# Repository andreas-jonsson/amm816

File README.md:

# AMM816

A homebrew CPU built from discrete logic.

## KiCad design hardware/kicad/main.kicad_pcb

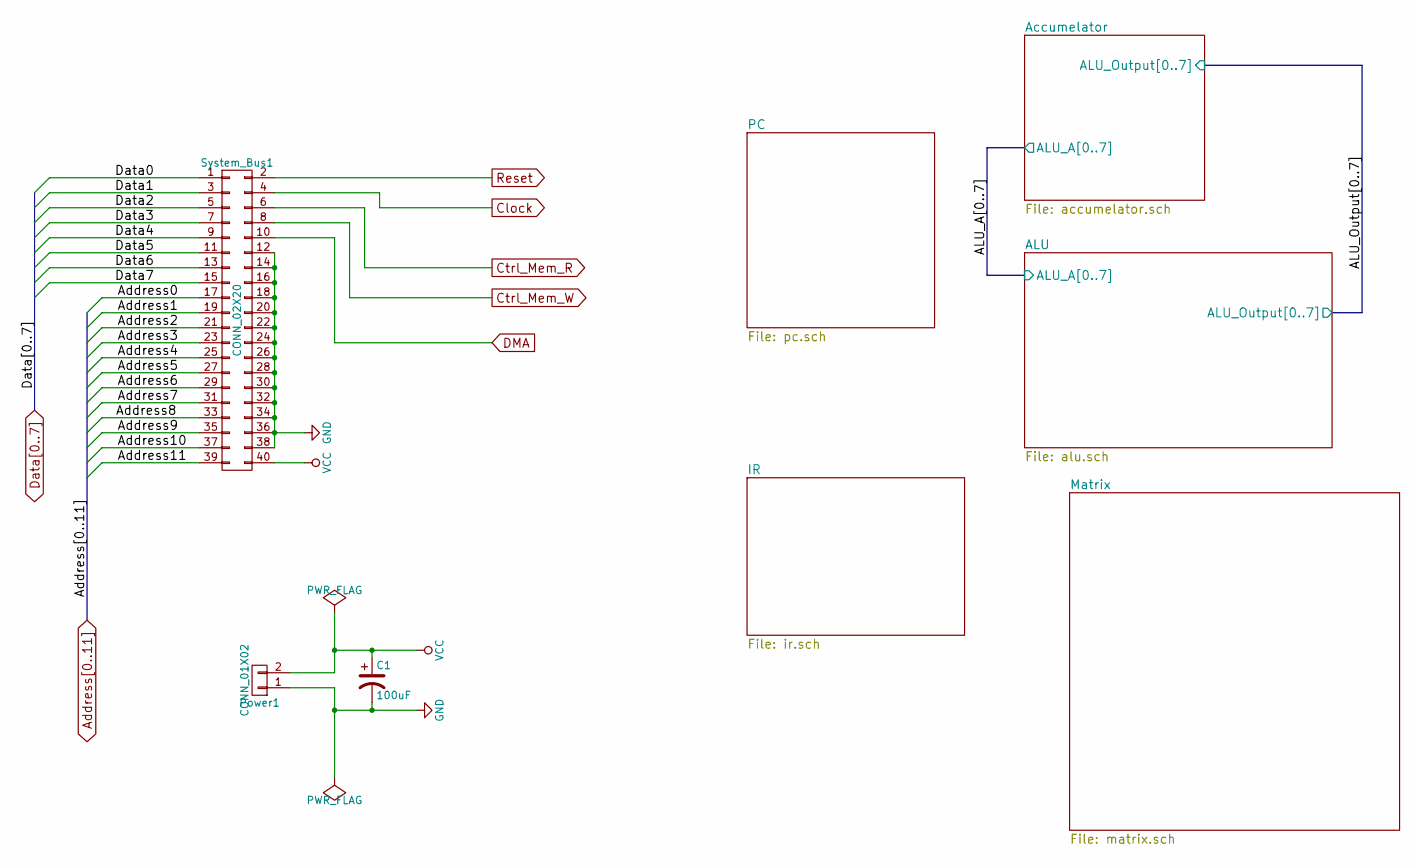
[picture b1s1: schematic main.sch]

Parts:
C1: 100uF; C_Radial_D5_L11_P2.5
Power1: CONN_01X02; Molex_KK-6410-02_02x2.54mm_Straight
System_Bus1: CONN_02X20; Pin_Header_Straight_2x20_Pitch2.00mm

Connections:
Address0: System_Bus1.17; also elsewhere on the board
Address1: System_Bus1.19; also elsewhere on the board
Address2: System_Bus1.21; also elsewhere on the board
Address3: System_Bus1.23; also elsewhere on the board
Address4: System_Bus1.25; also elsewhere on the board
Address5: System_Bus1.27; also elsewhere on the board
Address6: System_Bus1.29; also elsewhere on the board
Address7: System_Bus1.31; also elsewhere on the board
Address8: System_Bus1.33; also elsewhere on the board
Address9: System_Bus1.35; also elsewhere on the board
Address10: System_Bus1.37; also elsewhere on the board
Address11: System_Bus1.39; also elsewhere on the board
Clock: System_Bus1.4; also elsewhere on the board
Ctrl_Mem_R: System_Bus1.6; also elsewhere on the board
Ctrl_Mem_W: System_Bus1.8; also elsewhere on the board
DMA: System_Bus1.10; also elsewhere on the board
Data0: System_Bus1.1; also elsewhere on the board
Data1: System_Bus1.3; also elsewhere on the board
Data2: System_Bus1.5; also elsewhere on the board
Data3: System_Bus1.7; also elsewhere on the board
Data4: System_Bus1.9; also elsewhere on the board
Data5: System_Bus1.11; also elsewhere on the board
Data6: System_Bus1.13; also elsewhere on the board
Data7: System_Bus1.15; also elsewhere on the board
GND: C1.2, Power1.1, System_Bus1.12, System_Bus1.14, System_Bus1.16, System_Bus1.18, System_Bus1.20, System_Bus1.22, System_Bus1.24, System_Bus1.26, System_Bus1.28, System_Bus1.30, System_Bus1.32, System_Bus1.34, System_Bus1.36, System_Bus1.38; also elsewhere on the board
Reset: System_Bus1.2; also elsewhere on the board
VCC: C1.1, Power1.2, System_Bus1.40; also elsewhere on the board

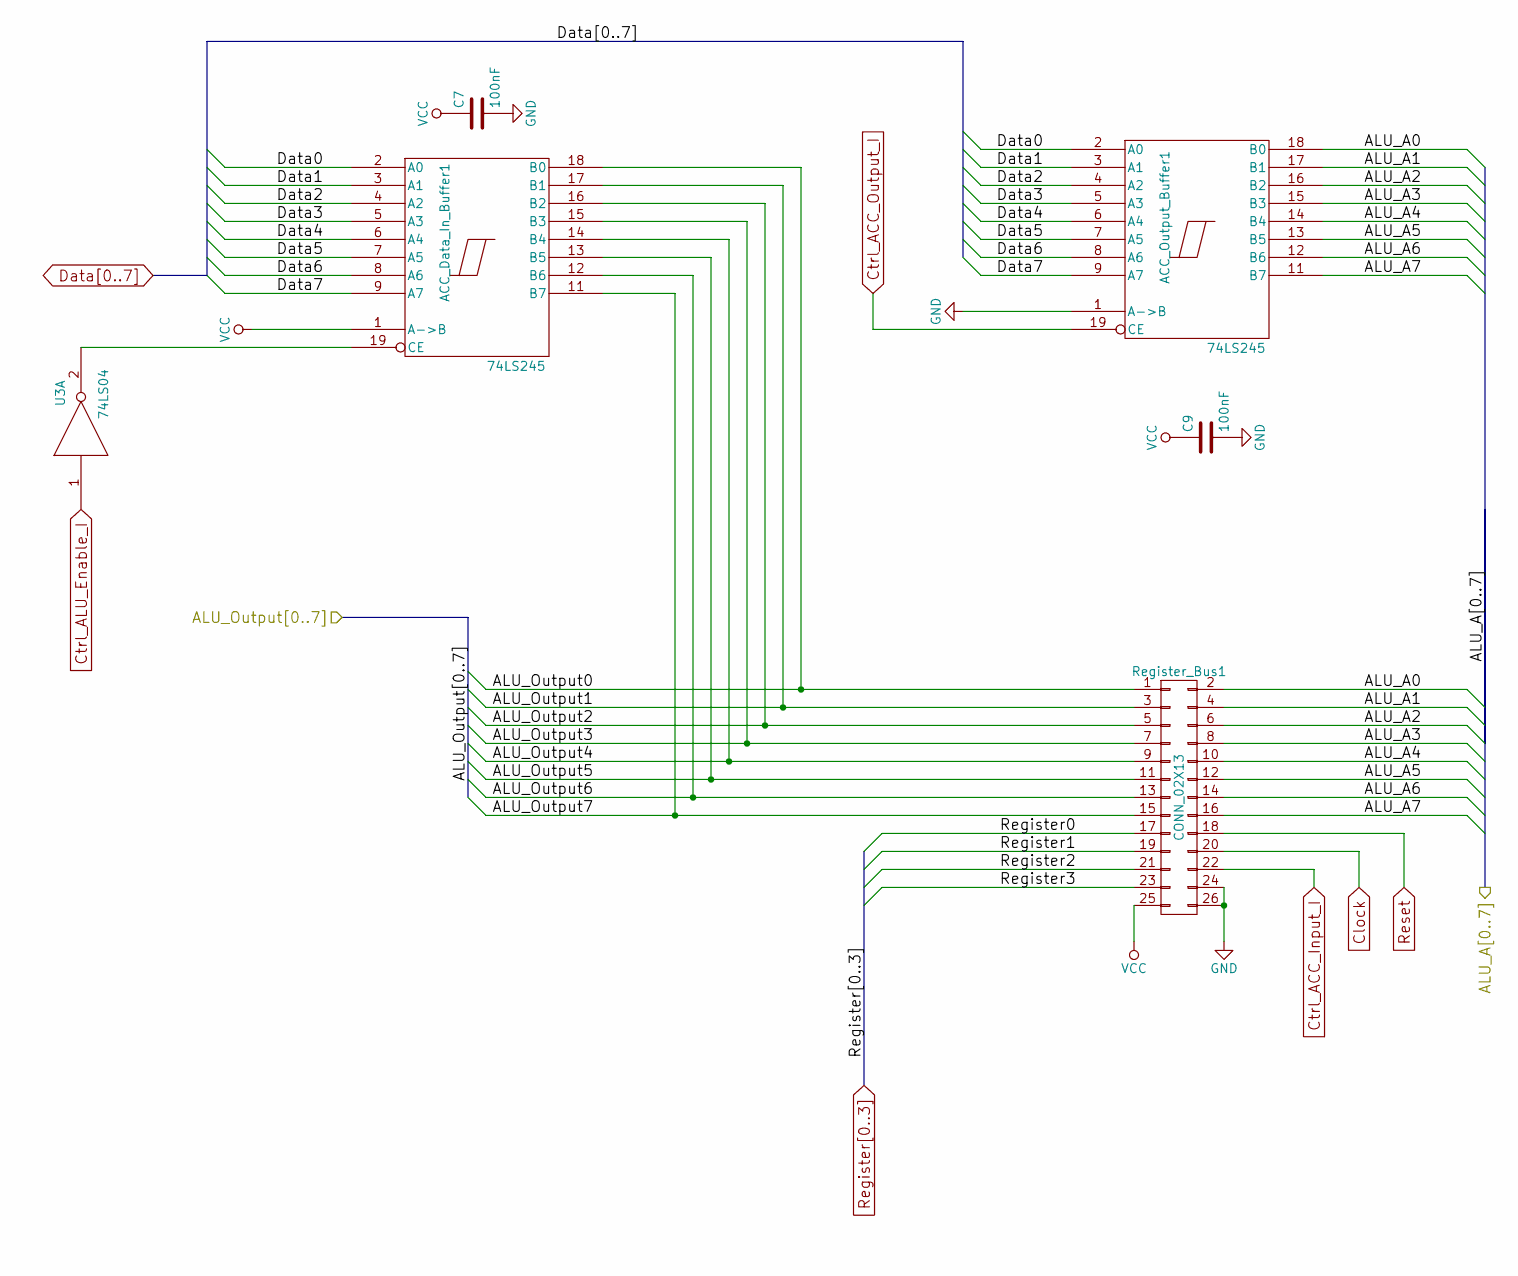
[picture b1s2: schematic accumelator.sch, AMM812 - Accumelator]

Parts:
ACC_Data_In_Buffer1: 74LS245; DIP-20_W7.62mm
ACC_Output_Buffer1: 74LS245; DIP-20_W7.62mm
C7, C9: 100nF; C_Disc_D3_P2.5
Register_Bus1: CONN_02X13; Pin_Header_Straight_2x13_Pitch2.00mm
U3: 74LS04; DIP-14_W7.62mm

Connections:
/ALU/ALU_A0: ACC_Output_Buffer1.18 (B0), Register_Bus1.2; also elsewhere on the board
/ALU/ALU_A1: ACC_Output_Buffer1.17 (B1), Register_Bus1.4; also elsewhere on the board
/ALU/ALU_A2: ACC_Output_Buffer1.16 (B2), Register_Bus1.6; also elsewhere on the board
/ALU/ALU_A3: ACC_Output_Buffer1.15 (B3), Register_Bus1.8; also elsewhere on the board
/ALU/ALU_A4: ACC_Output_Buffer1.14 (B4), Register_Bus1.10; also elsewhere on the board
/ALU/ALU_A5: ACC_Output_Buffer1.13 (B5), Register_Bus1.12; also elsewhere on the board
/ALU/ALU_A6: ACC_Output_Buffer1.12 (B6), Register_Bus1.14; also elsewhere on the board
/ALU/ALU_A7: ACC_Output_Buffer1.11 (B7), Register_Bus1.16; also elsewhere on the board
/ALU/ALU_Output0: ACC_Data_In_Buffer1.18 (B0), Register_Bus1.1; also elsewhere on the board
/ALU/ALU_Output1: ACC_Data_In_Buffer1.17 (B1), Register_Bus1.3; also elsewhere on the board
/ALU/ALU_Output2: ACC_Data_In_Buffer1.16 (B2), Register_Bus1.5; also elsewhere on the board
/ALU/ALU_Output3: ACC_Data_In_Buffer1.15 (B3), Register_Bus1.7; also elsewhere on the board
/ALU/ALU_Output4: ACC_Data_In_Buffer1.14 (B4), Register_Bus1.9; also elsewhere on the board
/ALU/ALU_Output5: ACC_Data_In_Buffer1.13 (B5), Register_Bus1.11; also elsewhere on the board
/ALU/ALU_Output6: ACC_Data_In_Buffer1.12 (B6), Register_Bus1.13; also elsewhere on the board
/ALU/ALU_Output7: ACC_Data_In_Buffer1.11 (B7), Register_Bus1.15; also elsewhere on the board
Clock: Register_Bus1.20; also elsewhere on the board
Ctrl_ACC_Input_I: Register_Bus1.22; also elsewhere on the board
Ctrl_ACC_Output_I: ACC_Output_Buffer1.19 (CE); also elsewhere on the board
Ctrl_ALU_Enable_I: U3.1; also elsewhere on the board
Data0: ACC_Data_In_Buffer1.2 (A0), ACC_Output_Buffer1.2 (A0); also elsewhere on the board
Data1: ACC_Data_In_Buffer1.3 (A1), ACC_Output_Buffer1.3 (A1); also elsewhere on the board
Data2: ACC_Data_In_Buffer1.4 (A2), ACC_Output_Buffer1.4 (A2); also elsewhere on the board
Data3: ACC_Data_In_Buffer1.5 (A3), ACC_Output_Buffer1.5 (A3); also elsewhere on the board
Data4: ACC_Data_In_Buffer1.6 (A4), ACC_Output_Buffer1.6 (A4); also elsewhere on the board
Data5: ACC_Data_In_Buffer1.7 (A5), ACC_Output_Buffer1.7 (A5); also elsewhere on the board
Data6: ACC_Data_In_Buffer1.8 (A6), ACC_Output_Buffer1.8 (A6); also elsewhere on the board
Data7: ACC_Data_In_Buffer1.9 (A7), ACC_Output_Buffer1.9 (A7); also elsewhere on the board
GND: ACC_Data_In_Buffer1.10 (GND), ACC_Output_Buffer1.1 (A->B), ACC_Output_Buffer1.10 (GND), C7.2, C9.2, Register_Bus1.24, Register_Bus1.26, U3.7 (GND); also elsewhere on the board
unnamed: ACC_Data_In_Buffer1.19 (CE), U3.2
Register0: Register_Bus1.17; also elsewhere on the board
Register1: Register_Bus1.19; also elsewhere on the board
Register2: Register_Bus1.21; also elsewhere on the board
Register3: Register_Bus1.23; also elsewhere on the board
Reset: Register_Bus1.18; also elsewhere on the board
VCC: ACC_Data_In_Buffer1.1 (A->B), ACC_Data_In_Buffer1.20 (VCC), ACC_Output_Buffer1.20 (VCC), C7.1, C9.1, Register_Bus1.25, U3.14 (VCC); also elsewhere on the board

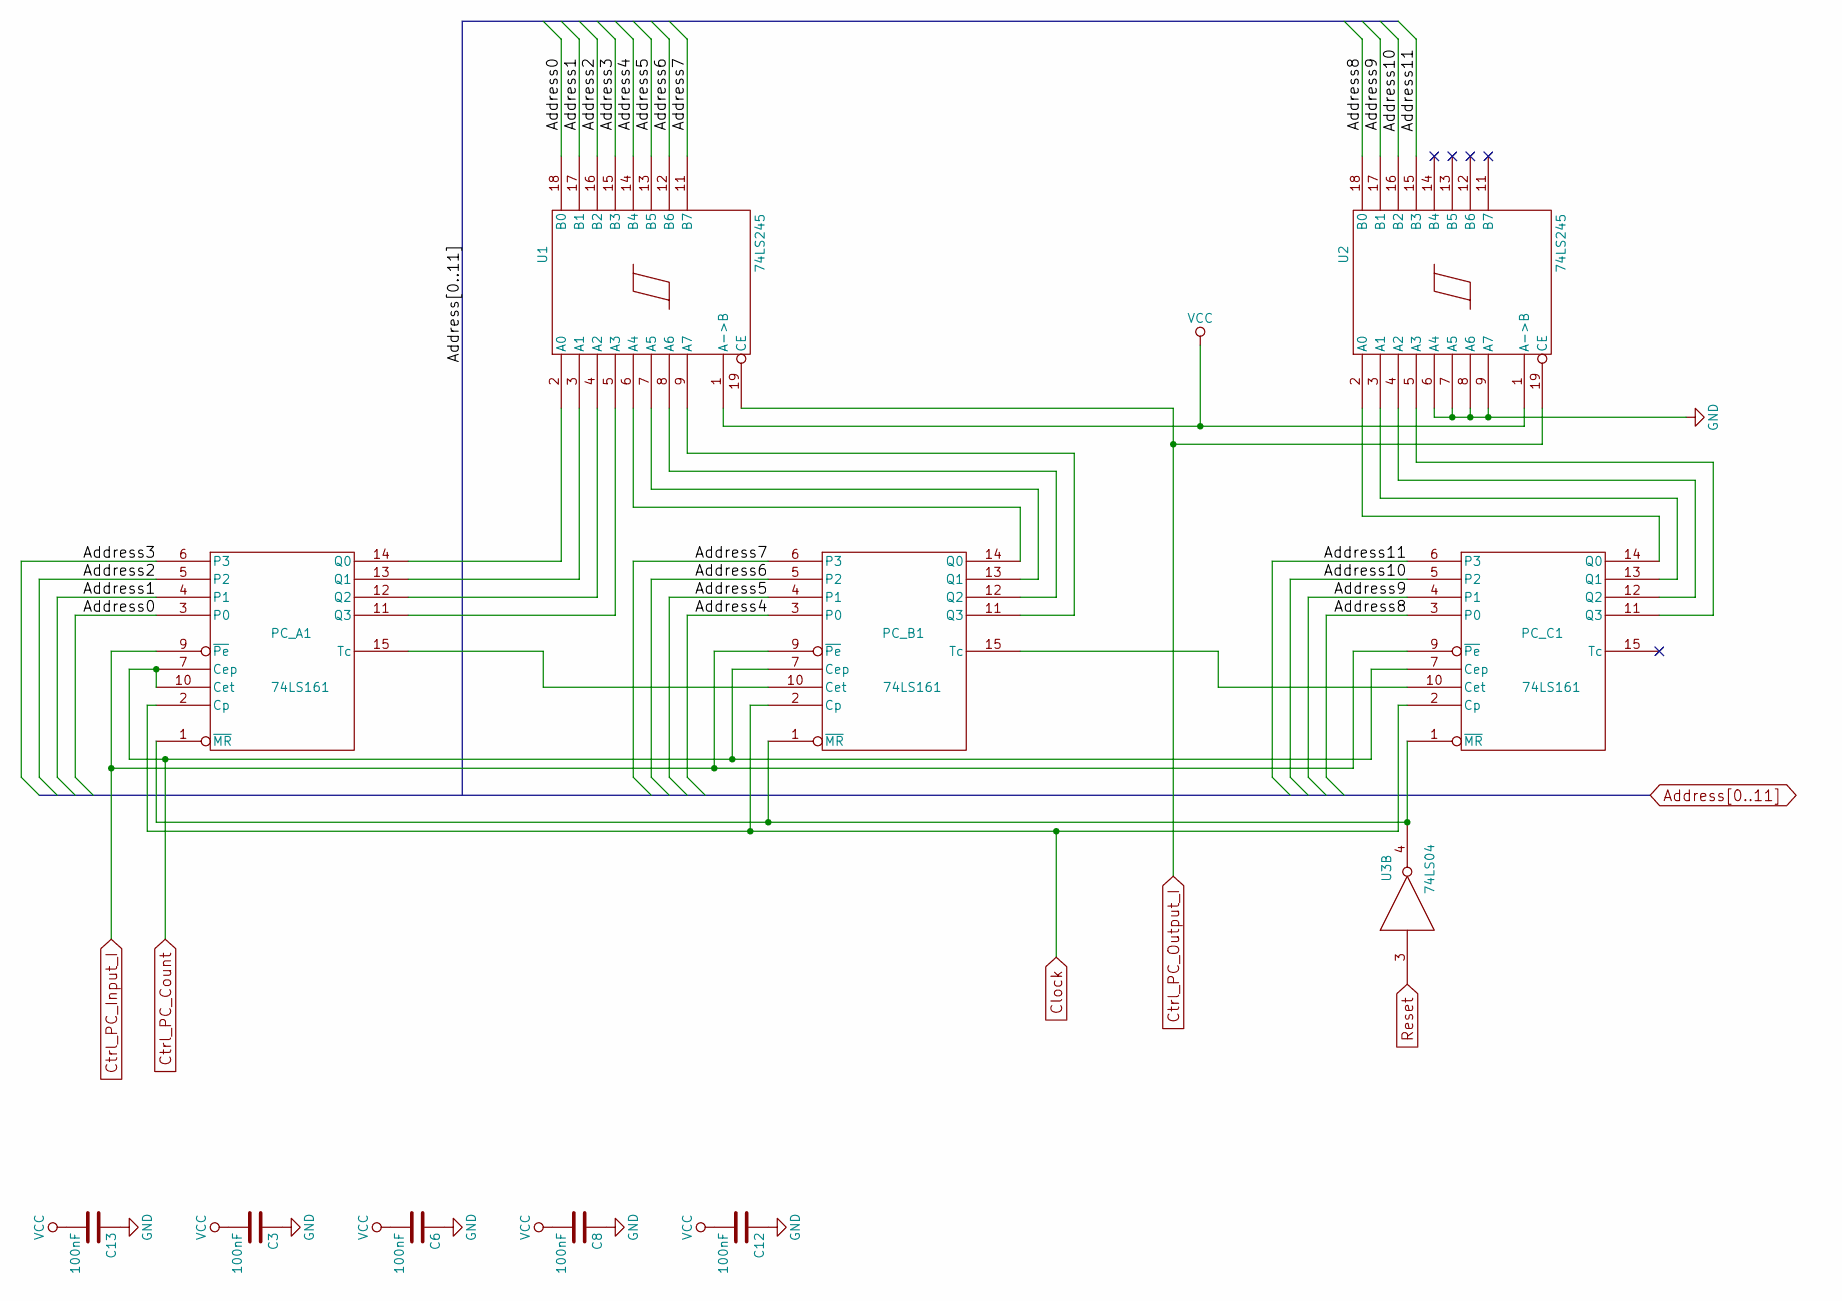
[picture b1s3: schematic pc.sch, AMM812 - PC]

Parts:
C3, C6, C8, C12, C13: 100nF; C_Disc_D3_P2.5
PC_A1: 74LS161; DIP-16_W7.62mm
PC_B1: 74LS161; DIP-16_W7.62mm
PC_C1: 74LS161; DIP-16_W7.62mm
U1, U2: 74LS245; DIP-20_W7.62mm
U3: 74LS04; DIP-14_W7.62mm

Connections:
Address0: PC_A1.3 (P0), U1.18 (B0); also elsewhere on the board
Address1: PC_A1.4 (P1), U1.17 (B1); also elsewhere on the board
Address2: PC_A1.5 (P2), U1.16 (B2); also elsewhere on the board
Address3: PC_A1.6 (P3), U1.15 (B3); also elsewhere on the board
Address4: PC_B1.3 (P0), U1.14 (B4); also elsewhere on the board
Address5: PC_B1.4 (P1), U1.13 (B5); also elsewhere on the board
Address6: PC_B1.5 (P2), U1.12 (B6); also elsewhere on the board
Address7: PC_B1.6 (P3), U1.11 (B7); also elsewhere on the board
Address8: PC_C1.3 (P0), U2.18 (B0); also elsewhere on the board
Address9: PC_C1.4 (P1), U2.17 (B1); also elsewhere on the board
Address10: PC_C1.5 (P2), U2.16 (B2); also elsewhere on the board
Address11: PC_C1.6 (P3), U2.15 (B3); also elsewhere on the board
Clock: PC_A1.2 (Cp), PC_B1.2 (Cp), PC_C1.2 (Cp); also elsewhere on the board
Ctrl_PC_Count: PC_A1.7 (Cep), PC_A1.10 (Cet), PC_B1.7 (Cep), PC_C1.7 (Cep); also elsewhere on the board
Ctrl_PC_Input_I: PC_A1.9 (~Pe), PC_B1.9 (~Pe), PC_C1.9 (~Pe); also elsewhere on the board
Ctrl_PC_Output_I: U1.19 (CE), U2.19 (CE); also elsewhere on the board
GND: C3.1, C6.1, C8.1, C12.1, C13.1, PC_A1.8 (GND), PC_B1.8 (GND), PC_C1.8 (GND), U1.10 (GND), U2.6 (A4), U2.7 (A5), U2.8 (A6), U2.9 (A7), U2.10 (GND), U3.7 (GND); also elsewhere on the board
unnamed: PC_A1.1 (~MR), PC_B1.1 (~MR), PC_C1.1 (~MR), U3.4
unnamed: PC_A1.11 (Q3), U1.5 (A3)
unnamed: PC_A1.12 (Q2), U1.4 (A2)
unnamed: PC_A1.13 (Q1), U1.3 (A1)
unnamed: PC_A1.14 (Q0), U1.2 (A0)
unnamed: PC_A1.15 (Tc), PC_B1.10 (Cet)
unnamed: PC_B1.11 (Q3), U1.9 (A7)
unnamed: PC_B1.12 (Q2), U1.8 (A6)
unnamed: PC_B1.13 (Q1), U1.7 (A5)
unnamed: PC_B1.14 (Q0), U1.6 (A4)
unnamed: PC_B1.15 (Tc), PC_C1.10 (Cet)
unnamed: PC_C1.11 (Q3), U2.5 (A3)
unnamed: PC_C1.12 (Q2), U2.4 (A2)
unnamed: PC_C1.13 (Q1), U2.3 (A1)
unnamed: PC_C1.14 (Q0), U2.2 (A0)
Reset: U3.3; also elsewhere on the board
VCC: C3.2, C6.2, C8.2, C12.2, C13.2, PC_A1.16 (VCC), PC_B1.16 (VCC), PC_C1.16 (VCC), U1.1 (A->B), U1.20 (VCC), U2.1 (A->B), U2.20 (VCC), U3.14 (VCC); also elsewhere on the board

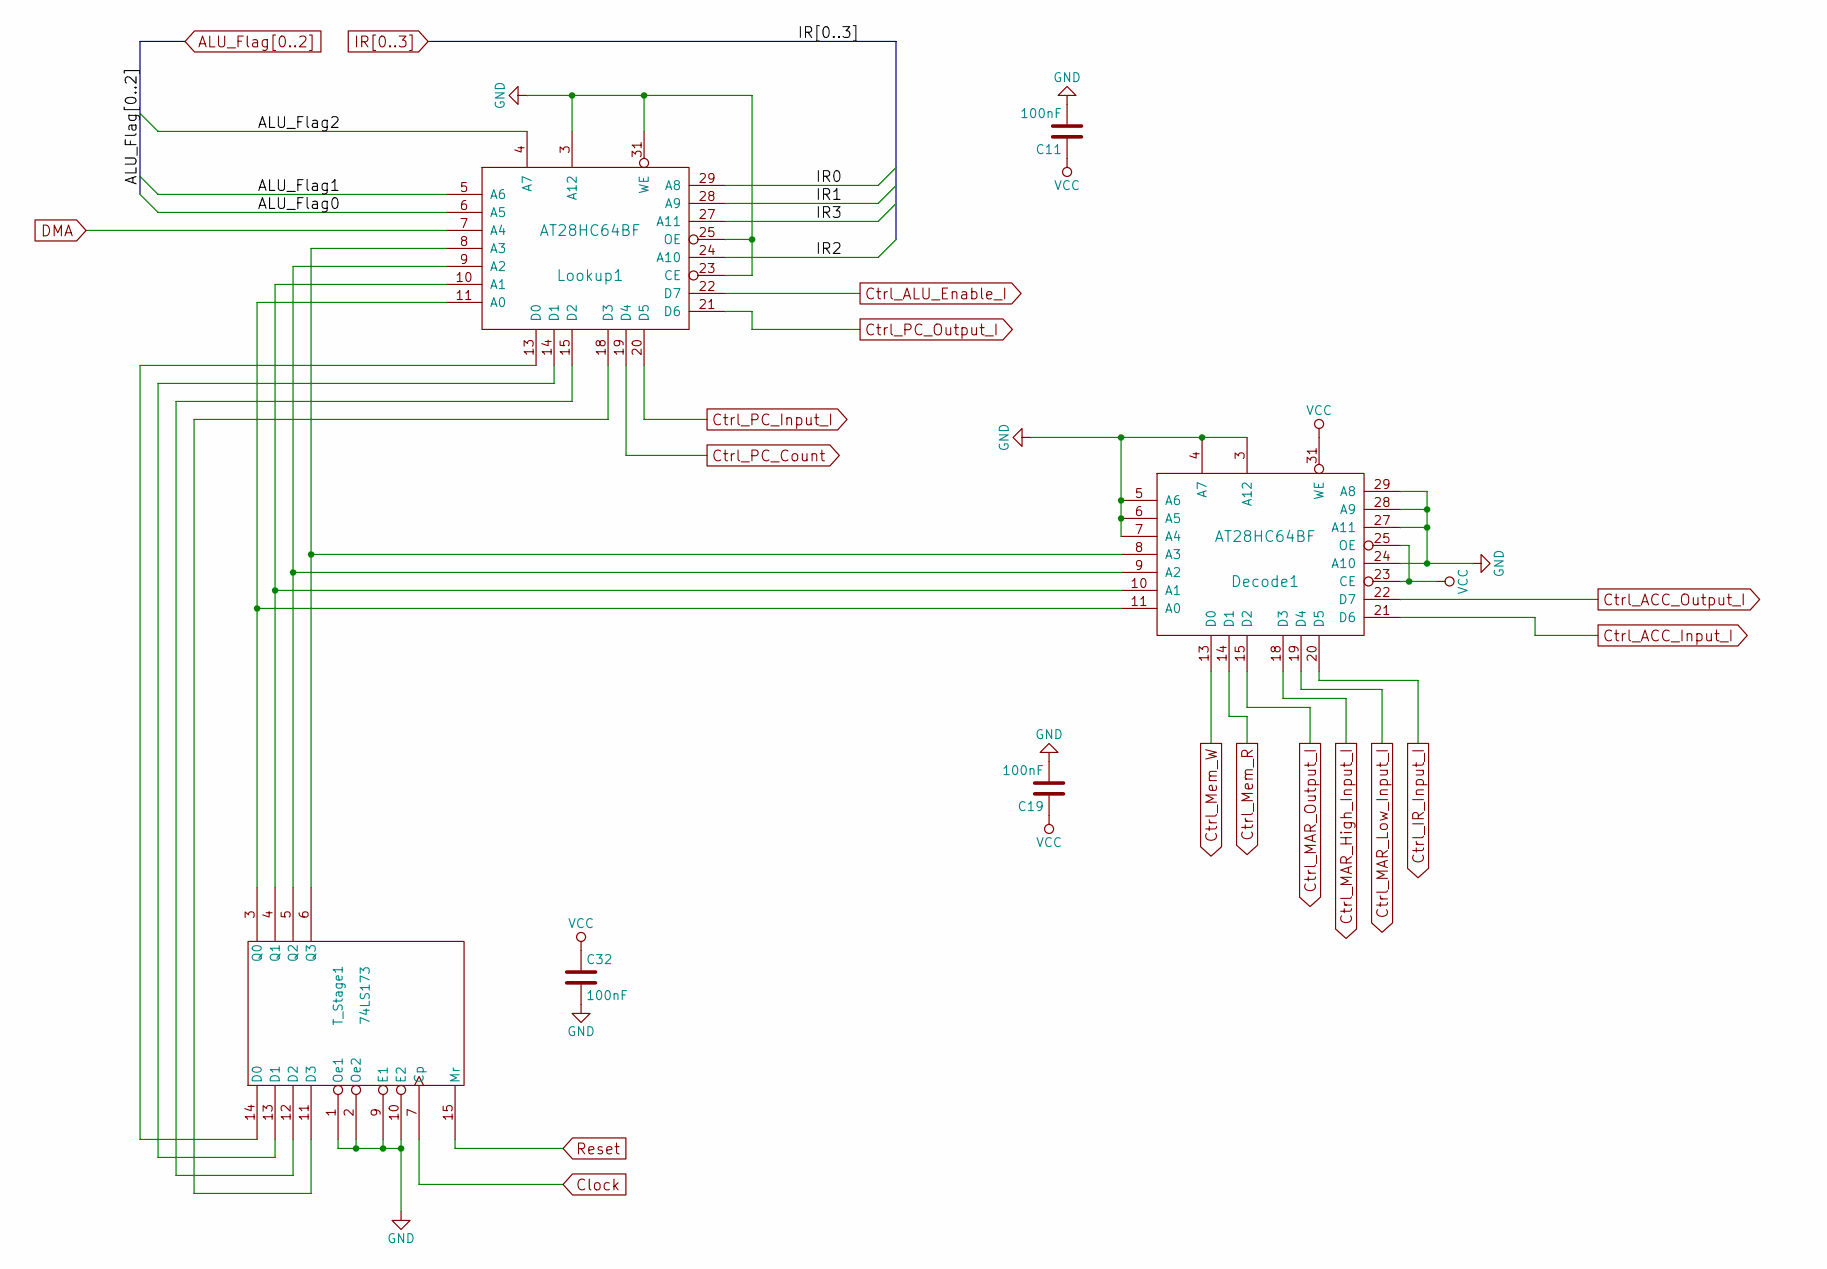
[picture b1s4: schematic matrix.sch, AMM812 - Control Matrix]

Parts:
C11, C19, C32: 100nF; C_Disc_D3_P2.5
Decode1: AT28HC64BF; PLCC-32_THT-Socket_bugfix
Lookup1: AT28HC64BF; PLCC-32_THT-Socket_bugfix
T_Stage1: 74LS173; DIP-16_W7.62mm

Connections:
ALU_Flag0: Lookup1.6 (A5); also elsewhere on the board
ALU_Flag1: Lookup1.5 (A6); also elsewhere on the board
ALU_Flag2: Lookup1.4 (A7); also elsewhere on the board
Clock: T_Stage1.7 (Cp); also elsewhere on the board
Ctrl_ACC_Input_I: Decode1.21 (D6); also elsewhere on the board
Ctrl_ACC_Output_I: Decode1.22 (D7); also elsewhere on the board
Ctrl_ALU_Enable_I: Lookup1.22 (D7); also elsewhere on the board
Ctrl_IR_Input_I: Decode1.20 (D5); also elsewhere on the board
Ctrl_MAR_High_Input_I: Decode1.18 (D3); also elsewhere on the board
Ctrl_MAR_Low_Input_I: Decode1.19 (D4); also elsewhere on the board
Ctrl_MAR_Output_I: Decode1.15 (D2); also elsewhere on the board
Ctrl_Mem_R: Decode1.14 (D1); also elsewhere on the board
Ctrl_Mem_W: Decode1.13 (D0); also elsewhere on the board
Ctrl_PC_Count: Lookup1.19 (D4); also elsewhere on the board
Ctrl_PC_Input_I: Lookup1.20 (D5); also elsewhere on the board
Ctrl_PC_Output_I: Lookup1.21 (D6); also elsewhere on the board
DMA: Lookup1.7 (A4); also elsewhere on the board
GND: C11.2, C19.2, C32.2, Decode1.3 (A12), Decode1.4 (A7), Decode1.5 (A6), Decode1.6 (A5), Decode1.7 (A4), Decode1.16 (GND), Decode1.24 (A10), Decode1.27 (A11), Decode1.28 (A9), Decode1.29 (A8), Lookup1.3 (A12), Lookup1.16 (GND), Lookup1.23 (CE), Lookup1.25 (OE), Lookup1.31 (WE), T_Stage1.1 (Oe1), T_Stage1.2 (Oe2), T_Stage1.8 (GND), T_Stage1.9 (E1), T_Stage1.10 (E2); also elsewhere on the board
IR0: Lookup1.29 (A8); also elsewhere on the board
IR1: Lookup1.28 (A9); also elsewhere on the board
IR2: Lookup1.24 (A10); also elsewhere on the board
IR3: Lookup1.27 (A11); also elsewhere on the board
unnamed: Decode1.8 (A3), Lookup1.8 (A3), T_Stage1.6 (Q3)
unnamed: Decode1.9 (A2), Lookup1.9 (A2), T_Stage1.5 (Q2)
unnamed: Decode1.10 (A1), Lookup1.10 (A1), T_Stage1.4 (Q1)
unnamed: Decode1.11 (A0), Lookup1.11 (A0), T_Stage1.3 (Q0)
unnamed: Lookup1.13 (D0), T_Stage1.14 (D0)
unnamed: Lookup1.14 (D1), T_Stage1.13 (D1)
unnamed: Lookup1.15 (D2), T_Stage1.12 (D2)
unnamed: Lookup1.18 (D3), T_Stage1.11 (D3)
Reset: T_Stage1.15 (Mr); also elsewhere on the board
VCC: C11.1, C19.1, C32.1, Decode1.23 (CE), Decode1.25 (OE), Decode1.31 (WE), Decode1.32 (VCC), Lookup1.32 (VCC), T_Stage1.16 (VCC); also elsewhere on the board

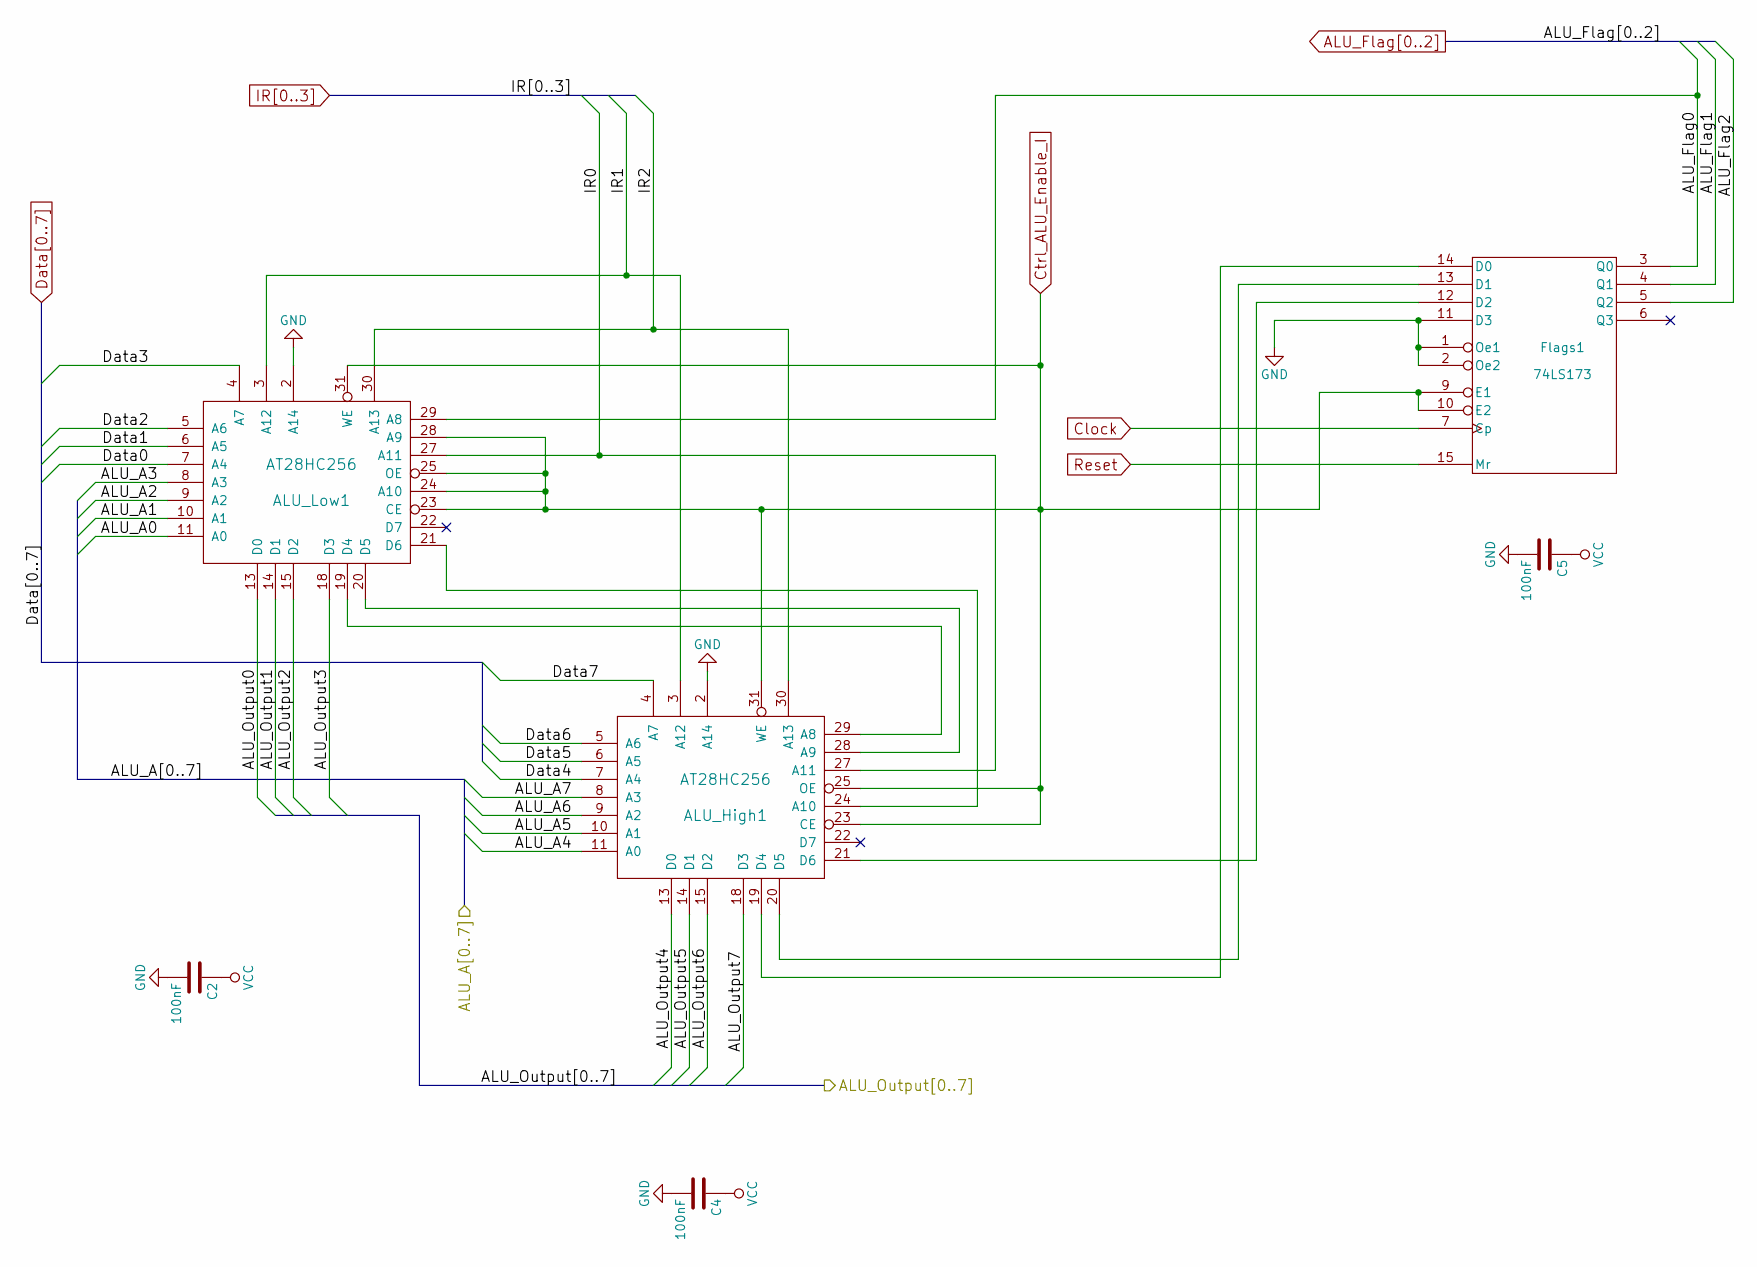
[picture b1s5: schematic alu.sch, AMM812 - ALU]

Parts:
ALU_High1: AT28HC256; PLCC-32_THT-Socket_bugfix
ALU_Low1: AT28HC256; PLCC-32_THT-Socket_bugfix
C2, C4, C5: 100nF; C_Disc_D3_P2.5
Flags1: 74LS173; DIP-16_W7.62mm

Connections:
/ALU/ALU_A0: ALU_Low1.11 (A0); also elsewhere on the board
/ALU/ALU_A1: ALU_Low1.10 (A1); also elsewhere on the board
/ALU/ALU_A2: ALU_Low1.9 (A2); also elsewhere on the board
/ALU/ALU_A3: ALU_Low1.8 (A3); also elsewhere on the board
/ALU/ALU_A4: ALU_High1.11 (A0); also elsewhere on the board
/ALU/ALU_A5: ALU_High1.10 (A1); also elsewhere on the board
/ALU/ALU_A6: ALU_High1.9 (A2); also elsewhere on the board
/ALU/ALU_A7: ALU_High1.8 (A3); also elsewhere on the board
/ALU/ALU_Output0: ALU_Low1.13 (D0); also elsewhere on the board
/ALU/ALU_Output1: ALU_Low1.14 (D1); also elsewhere on the board
/ALU/ALU_Output2: ALU_Low1.15 (D2); also elsewhere on the board
/ALU/ALU_Output3: ALU_Low1.18 (D3); also elsewhere on the board
/ALU/ALU_Output4: ALU_High1.13 (D0); also elsewhere on the board
/ALU/ALU_Output5: ALU_High1.14 (D1); also elsewhere on the board
/ALU/ALU_Output6: ALU_High1.15 (D2); also elsewhere on the board
/ALU/ALU_Output7: ALU_High1.18 (D3); also elsewhere on the board
ALU_Flag0: ALU_Low1.29 (A8), Flags1.3 (Q0); also elsewhere on the board
ALU_Flag1: Flags1.4 (Q1); also elsewhere on the board
ALU_Flag2: Flags1.5 (Q2); also elsewhere on the board
Clock: Flags1.7 (Cp); also elsewhere on the board
Ctrl_ALU_Enable_I: ALU_High1.23 (CE), ALU_High1.25 (OE), ALU_High1.31 (WE), ALU_Low1.23 (CE), ALU_Low1.24 (A10), ALU_Low1.25 (OE), ALU_Low1.28 (A9), ALU_Low1.31 (WE), Flags1.9 (E1), Flags1.10 (E2); also elsewhere on the board
Data0: ALU_Low1.7 (A4); also elsewhere on the board
Data1: ALU_Low1.6 (A5); also elsewhere on the board
Data2: ALU_Low1.5 (A6); also elsewhere on the board
Data3: ALU_Low1.4 (A7); also elsewhere on the board
Data4: ALU_High1.7 (A4); also elsewhere on the board
Data5: ALU_High1.6 (A5); also elsewhere on the board
Data6: ALU_High1.5 (A6); also elsewhere on the board
Data7: ALU_High1.4 (A7); also elsewhere on the board
GND: ALU_High1.2 (A14), ALU_High1.16 (GND), ALU_Low1.2 (A14), ALU_Low1.16 (GND), C2.2, C4.2, C5.2, Flags1.1 (Oe1), Flags1.2 (Oe2), Flags1.8 (GND), Flags1.11 (D3); also elsewhere on the board
IR0: ALU_High1.27 (A11), ALU_Low1.27 (A11); also elsewhere on the board
IR1: ALU_High1.3 (A12), ALU_Low1.3 (A12); also elsewhere on the board
IR2: ALU_High1.30 (A13), ALU_Low1.30 (A13); also elsewhere on the board
unnamed: ALU_High1.19 (D4), Flags1.14 (D0)
unnamed: ALU_High1.20 (D5), Flags1.13 (D1)
unnamed: ALU_High1.21 (D6), Flags1.12 (D2)
unnamed: ALU_High1.24 (A10), ALU_Low1.21 (D6)
unnamed: ALU_High1.28 (A9), ALU_Low1.20 (D5)
unnamed: ALU_High1.29 (A8), ALU_Low1.19 (D4)
Reset: Flags1.15 (Mr); also elsewhere on the board
VCC: ALU_High1.32 (VCC), ALU_Low1.32 (VCC), C2.1, C4.1, C5.1, Flags1.16 (VCC); also elsewhere on the board

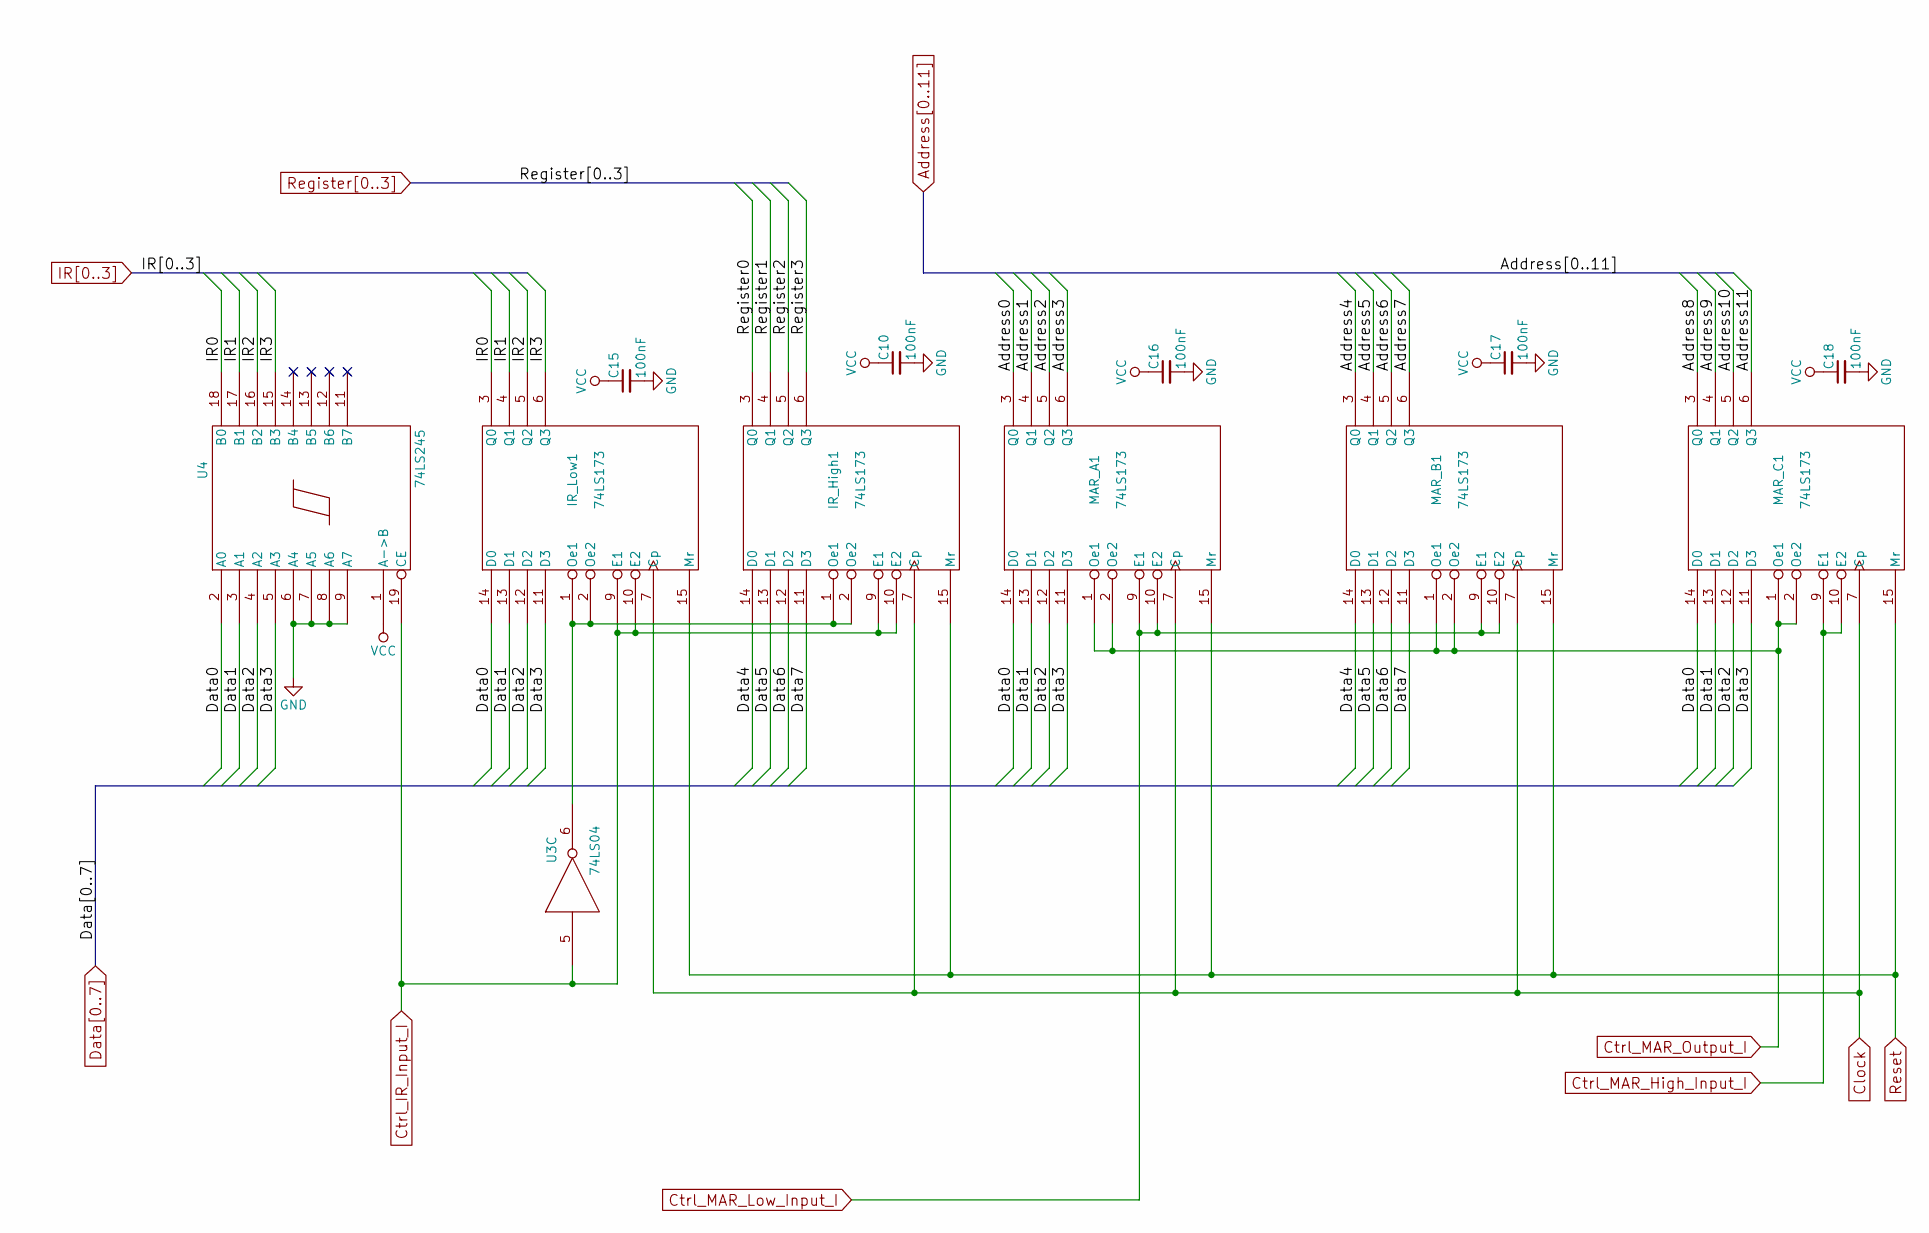
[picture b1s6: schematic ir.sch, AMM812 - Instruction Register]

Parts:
C10, C15, C16, C17, C18: 100nF; C_Disc_D3_P2.5
IR_High1: 74LS173; DIP-16_W7.62mm
IR_Low1: 74LS173; DIP-16_W7.62mm
MAR_A1: 74LS173; DIP-16_W7.62mm
MAR_B1: 74LS173; DIP-16_W7.62mm
MAR_C1: 74LS173; DIP-16_W7.62mm
U3: 74LS04
U4: 74LS245; DIP-20_W7.62mm

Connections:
Address0: MAR_A1.3 (Q0); also elsewhere on the board
Address1: MAR_A1.4 (Q1); also elsewhere on the board
Address2: MAR_A1.5 (Q2); also elsewhere on the board
Address3: MAR_A1.6 (Q3); also elsewhere on the board
Address4: MAR_B1.3 (Q0); also elsewhere on the board
Address5: MAR_B1.4 (Q1); also elsewhere on the board
Address6: MAR_B1.5 (Q2); also elsewhere on the board
Address7: MAR_B1.6 (Q3); also elsewhere on the board
Address8: MAR_C1.3 (Q0); also elsewhere on the board
Address9: MAR_C1.4 (Q1); also elsewhere on the board
Address10: MAR_C1.5 (Q2); also elsewhere on the board
Address11: MAR_C1.6 (Q3); also elsewhere on the board
Clock: IR_High1.7 (Cp), IR_Low1.7 (Cp), MAR_A1.7 (Cp), MAR_B1.7 (Cp), MAR_C1.7 (Cp); also elsewhere on the board
Ctrl_IR_Input_I: IR_High1.9 (E1), IR_High1.10 (E2), IR_Low1.9 (E1), IR_Low1.10 (E2), U3.5, U4.19 (CE); also elsewhere on the board
Ctrl_MAR_High_Input_I: MAR_C1.9 (E1), MAR_C1.10 (E2); also elsewhere on the board
Ctrl_MAR_Low_Input_I: MAR_A1.9 (E1), MAR_A1.10 (E2), MAR_B1.9 (E1), MAR_B1.10 (E2); also elsewhere on the board
Ctrl_MAR_Output_I: MAR_A1.1 (Oe1), MAR_A1.2 (Oe2), MAR_B1.1 (Oe1), MAR_B1.2 (Oe2), MAR_C1.1 (Oe1), MAR_C1.2 (Oe2); also elsewhere on the board
Data0: IR_Low1.14 (D0), MAR_A1.14 (D0), MAR_C1.14 (D0), U4.2 (A0); also elsewhere on the board
Data1: IR_Low1.13 (D1), MAR_A1.13 (D1), MAR_C1.13 (D1), U4.3 (A1); also elsewhere on the board
Data2: IR_Low1.12 (D2), MAR_A1.12 (D2), MAR_C1.12 (D2), U4.4 (A2); also elsewhere on the board
Data3: IR_Low1.11 (D3), MAR_A1.11 (D3), MAR_C1.11 (D3), U4.5 (A3); also elsewhere on the board
Data4: IR_High1.14 (D0), MAR_B1.14 (D0); also elsewhere on the board
Data5: IR_High1.13 (D1), MAR_B1.13 (D1); also elsewhere on the board
Data6: IR_High1.12 (D2), MAR_B1.12 (D2); also elsewhere on the board
Data7: IR_High1.11 (D3), MAR_B1.11 (D3); also elsewhere on the board
GND: C10.2, C15.2, C16.2, C17.2, C18.2, IR_High1.8 (GND), IR_Low1.8 (GND), MAR_A1.8 (GND), MAR_B1.8 (GND), MAR_C1.8 (GND), U3.7 (GND), U4.6 (A4), U4.7 (A5), U4.8 (A6), U4.9 (A7), U4.10 (GND); also elsewhere on the board
IR0: IR_Low1.3 (Q0), U4.18 (B0); also elsewhere on the board
IR1: IR_Low1.4 (Q1), U4.17 (B1); also elsewhere on the board
IR2: IR_Low1.5 (Q2), U4.16 (B2); also elsewhere on the board
IR3: IR_Low1.6 (Q3), U4.15 (B3); also elsewhere on the board
unnamed: IR_High1.1 (Oe1), IR_High1.2 (Oe2), IR_Low1.1 (Oe1), IR_Low1.2 (Oe2), U3.6
Register0: IR_High1.3 (Q0); also elsewhere on the board
Register1: IR_High1.4 (Q1); also elsewhere on the board
Register2: IR_High1.5 (Q2); also elsewhere on the board
Register3: IR_High1.6 (Q3); also elsewhere on the board
Reset: IR_High1.15 (Mr), IR_Low1.15 (Mr), MAR_A1.15 (Mr), MAR_B1.15 (Mr), MAR_C1.15 (Mr); also elsewhere on the board
VCC: C10.1, C15.1, C16.1, C17.1, C18.1, IR_High1.16 (VCC), IR_Low1.16 (VCC), MAR_A1.16 (VCC), MAR_B1.16 (VCC), MAR_C1.16 (VCC), U3.14 (VCC), U4.1 (A->B), U4.20 (VCC); also elsewhere on the board

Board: 2 copper layers, 46 parts (0 on the bottom side), 95 nets, no tracks yet.

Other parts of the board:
REF1, REF2, REF3, REF4: 1pin

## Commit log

2018-10-03 Just a backup.
2018-10-11 Add .gitlab-ci.yml
2018-10-12 Another backup.
2018-10-15 Updated text.
2018-10-19 Just a backup

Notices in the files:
hardware/kicad/main.kicad_pcb:
Copyright © 2018 Andreas T Jonsson
